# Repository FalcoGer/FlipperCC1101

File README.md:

# FlipperCC1101
Adapter for an external CC1101 module for the Flipper Zero

## How to use:
1. Solder on 90° Pin headers to connect to the flipper.
2. Solder on a 2x4 pin header onto your CC1101 Module
3. Solder on a 470 Ohm resistor and LED (optional)
4. Solder on a AMS1117 5V to 3.3V DC to DC step down converter.
5. Solder on a capacitor (probably optional)
6. Solder the C1101 Module onto this board. (Pin 1 is GND)
7. Install Flipper firmware that is capable of using the CC1101 Module (Unleashed or RogueMaster)
8. Hack the planet

## Images

### Render

### Front View

### Rear View

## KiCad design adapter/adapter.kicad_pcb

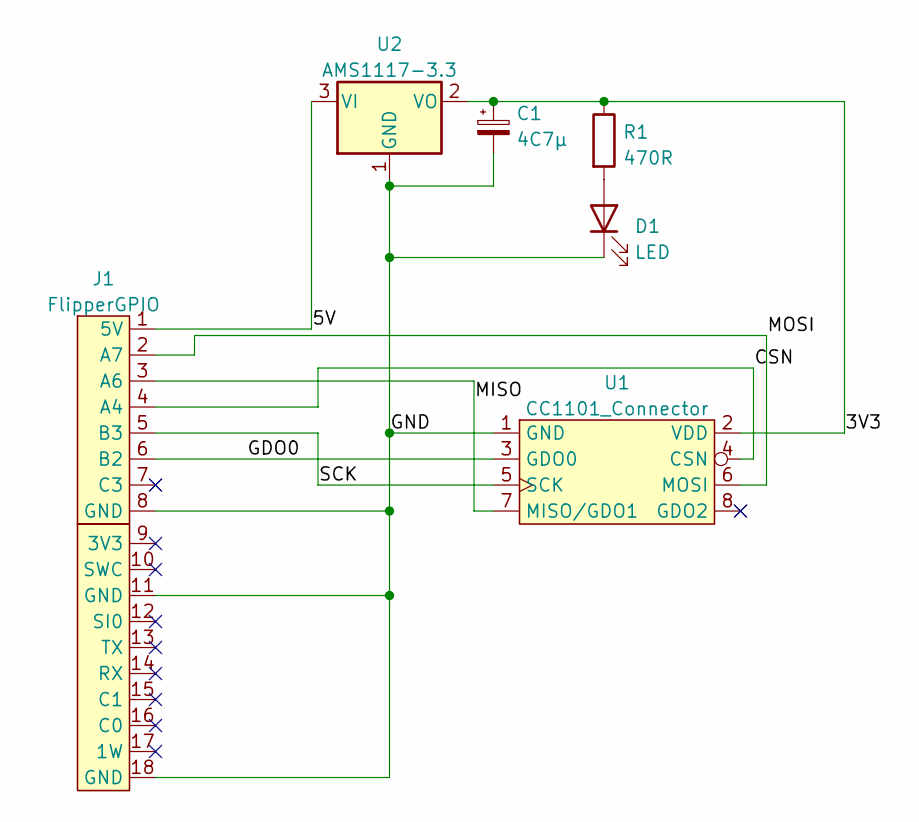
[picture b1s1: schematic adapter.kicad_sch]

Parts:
C1: 4C7µ; CP_Radial_D4.0mm_P2.00mm
D1: LED; LED_D3.0mm
J1: FlipperGPIO
R1: 470R; R_Axial_DIN0207_L6.3mm_D2.5mm_P7.62mm_Horizontal
U1: CC1101_Connector; PinHeader_2x04_P2.54mm_Vertical
U2: AMS1117-3.3; PinHeader_1x03_P2.54mm_Vertical

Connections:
/3V3: C1.1, R1.1, U1.2 (VDD), U2.2 (VO)
/5V: J1.1 (5V), U2.3 (VI)
/CSN: J1.4 (A4), U1.4 (CSN)
/GDO0: J1.6 (B2), U1.3 (GDO0)
/GND: C1.2, D1.1 (K), J1.8 (GND), J1.11 (GND), J1.18 (GND), U1.1 (GND), U2.1 (GND)
/MISO: J1.3 (A6), U1.7 (MISO/GDO1)
/MOSI: J1.2 (A7), U1.6 (MOSI)
/SCK: J1.5 (B3), U1.5 (SCK)
unnamed: D1.2 (A), R1.2

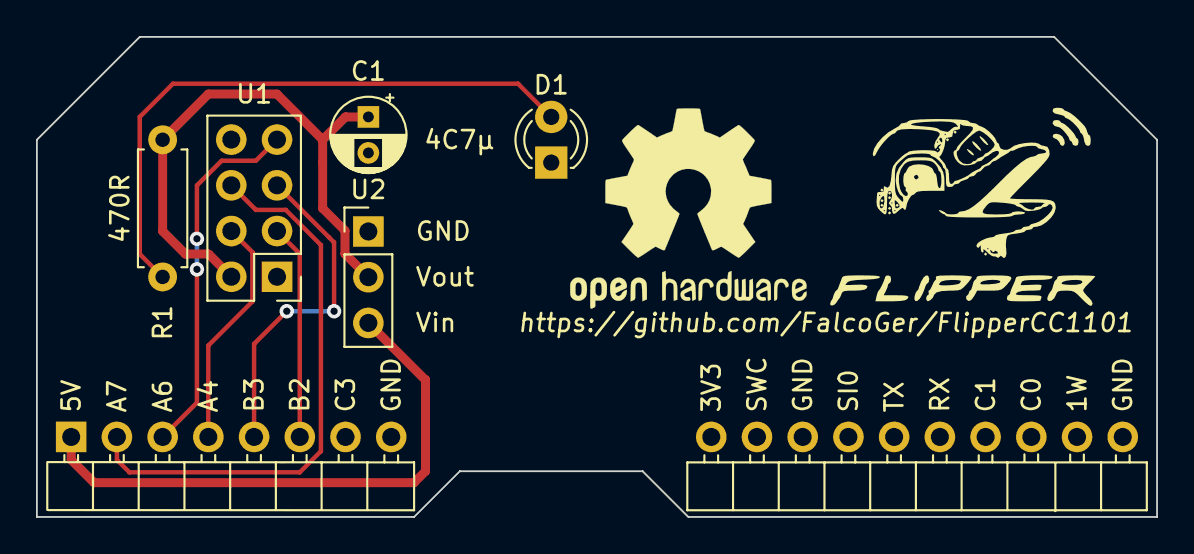
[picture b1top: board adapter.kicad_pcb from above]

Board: 2 copper layers, 62.2 x 26.7 mm, 6 parts (0 on the bottom side), 9 nets.

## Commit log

2023-08-29 ignore export outputs
2023-08-29 moved kicad project files to separate directory
2023-08-29 adds images
2023-08-29 ignore gerber zip file
2023-08-30 include a 5V to 3.3V buck converter for more reliable power supply update to include a power LED since 5V is not always active
2023-08-30 rearranged board layout to make space for the buck converter
2023-08-30 slightly increase board size to clear PCB checker errors.
